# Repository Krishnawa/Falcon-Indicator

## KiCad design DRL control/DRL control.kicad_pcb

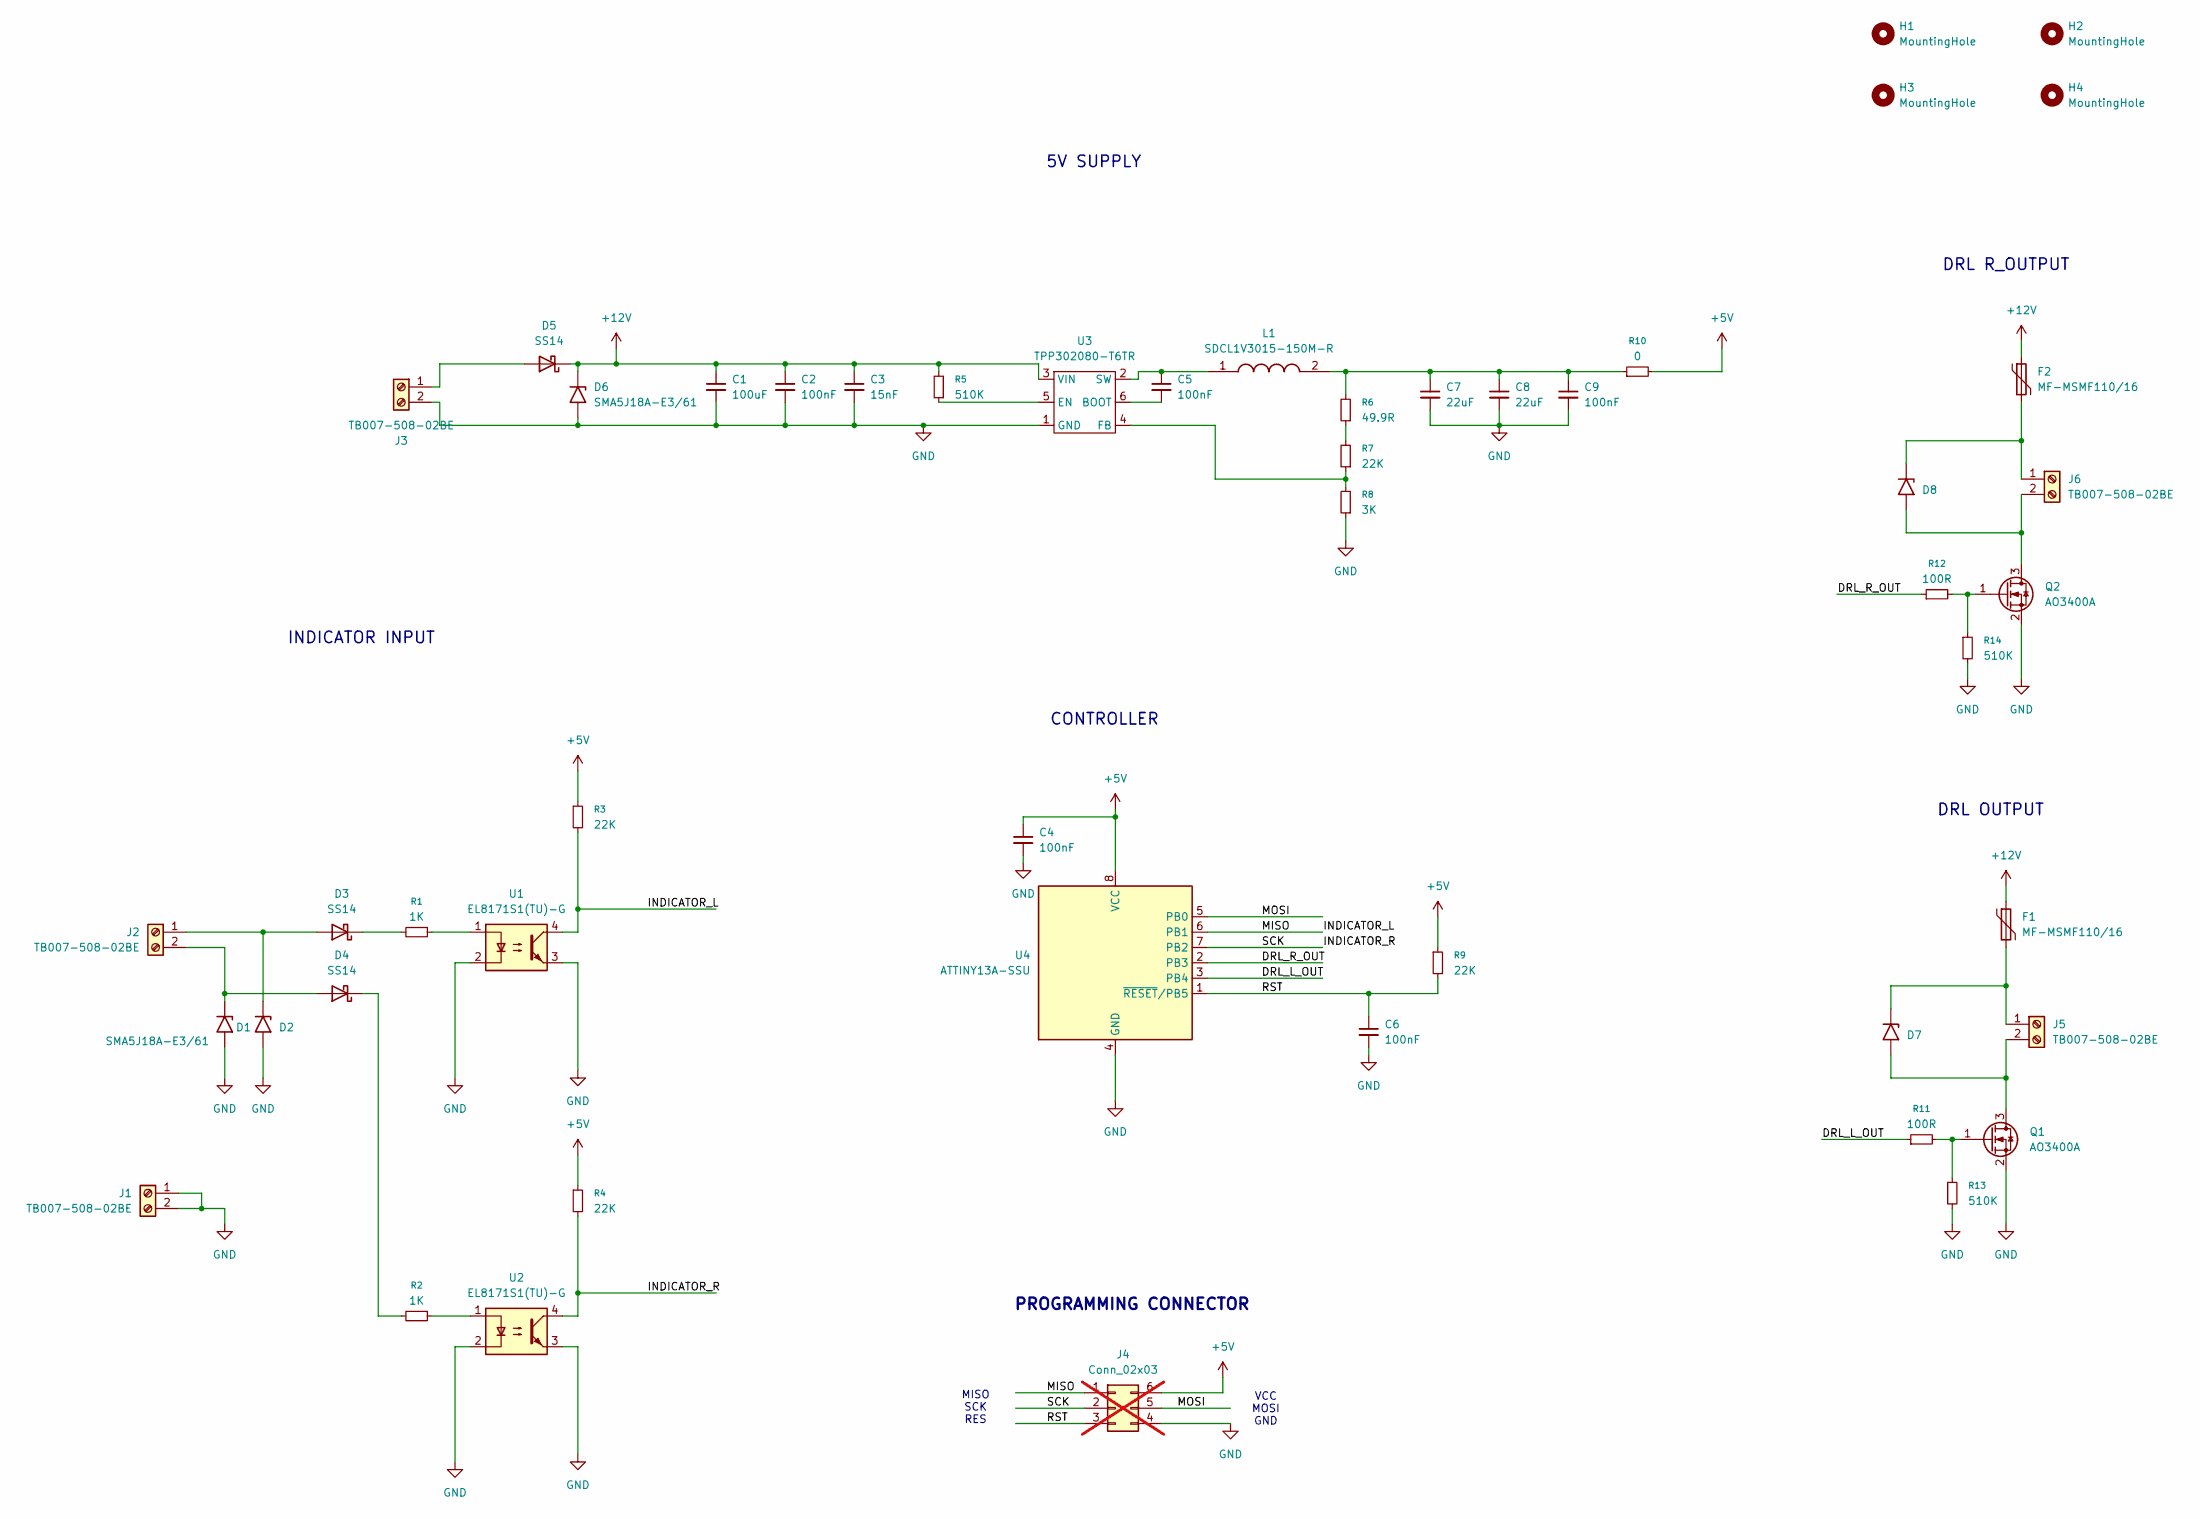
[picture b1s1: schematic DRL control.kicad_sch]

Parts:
C1: 100uF; CP_Elec_6.3x7.7; Mouser Part Number UWT1V101MCL1GS
C2, C4, C5, C6, C9: 100nF; C_0603_1608Metric_Pad1.08x0.95mm_HandSolder; Mouser Part Number CML0603X7R104KT50V
C3: 15nF; C_0603_1608Metric_Pad1.08x0.95mm_HandSolder; Mouser Part Number CGA3E2X7R1H153M080AA
C7, C8: 22uF; CP_Elec_5x3; Mouser Part Number EDH226M016S9DAA
D1, D2, D6, D7, D8: SMA5J18A-E3/61; D_SMA; Mouser Part Number SMA5J18A-E3/61
D3, D4, D5: SS14; D_SMA; Mouser Part Number SS14
F1, F2: MF-MSMF110/16; Fuse_1812_4532Metric_Pad1.30x3.40mm_HandSolder; Mouser Part Number MF-MSMF110/16
H1, H2, H3, H4: MountingHole; MountingHole_2mm
J1, J2, J3, J5, J6: TB007-508-02BE; TerminalBlock_CUI_TB007-508-02_1x02_P5.08mm_Horizontal; Mouser Part Number TB007-508-02BE
J4: Conn_02x03; IDC-Header_2x03_P2.54mm_Vertical; Mouser Part Number 826632-3; not fitted
L1: SDCL1V3015-150M-R; SDCL1V3015150MR; Mouser Part Number SDCL1V3015-150M-R
Q1, Q2: AO3400A; SOT-23; Mouser Part Number AO3400A
R1, R2: 1K; R_0805_2012Metric_Pad1.20x1.40mm_HandSolder; Mouser Part Number RK73H2ATTDD1001F
R3, R4, R7, R9: 22K; R_0603_1608Metric_Pad0.98x0.95mm_HandSolder; Mouser Part Number CR0603-FX-2202ELF
R5, R13, R14: 510K; R_0603_1608Metric_Pad0.98x0.95mm_HandSolder; Mouser Part Number RC0603FR-07510KL
R6: 49.9R; R_0603_1608Metric_Pad0.98x0.95mm_HandSolder; Mouser Part Number MCT06030C4999FP500
R8: 3K; R_0603_1608Metric_Pad0.98x0.95mm_HandSolder; Mouser Part Number ERJ-3EKF3001V
R10: 0; R_0805_2012Metric_Pad1.20x1.40mm_HandSolder; Mouser Part Number RCS08050000Z0EA
R11, R12: 100R; R_0603_1608Metric_Pad0.98x0.95mm_HandSolder; Mouser Part Number CRT0603-DY-1000ELF
U1, U2: EL8171S1(TU)-G; DIP-4_W8.89mm_SMDSocket_LongPads; Mouser Part Number EL8171S1(TU)-G
U3: TPP302080-T6TR; SOT-23-6_Handsoldering; Mouser Part Number TPP302080-T6TR
U4: ATTINY13A-SSU; SOIC-8_3.9x4.9mm_P1.27mm; Mouser Part Number ATTINY13A-SSU

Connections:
+5V: C4.1, J4.6, R3.1, R4.1, R9.1, R10.2, U4.8 (VCC)
+12V: C1.1, C2.1, C3.1, D5.1 (K), D6.1 (A1), F1.1, F2.1, R5.2, U3.3 (VIN)
/DRL_L_OUT: R11.1, U4.3 (PB4)
/DRL_R_OUT: R12.1, U4.2 (PB3)
/INDICATOR_L: J4.1, R3.2, U1.4, U4.6 (PB1)
/INDICATOR_R: J4.2, R4.2, U2.4, U4.7 (PB2)
/MOSI: J4.5, U4.5 (PB0)
/RST: C6.1, J4.3, R9.2, U4.1 (~RESET/PB5)
GND: C1.2, C2.2, C3.2, C4.2, C6.2, C7.2, C8.2, C9.2, D1.2 (A2), D2.2 (A2), D6.2 (A2), J1.1, J1.2, J3.2, J4.4, Q1.2 (S), Q2.2 (S), R8.1, R13.2, R14.2, U1.2, U1.3, U2.2, U2.3, U3.1 (GND), U4.4 (GND)
unnamed: C7.1, C8.1, C9.1, L1.2, R6.2, R10.1
unnamed: D1.1 (A1), D4.2 (A), J2.2
unnamed: D2.1 (A1), D3.2 (A), J2.1
unnamed: D3.1 (K), R1.2
unnamed: D4.1 (K), R2.2
unnamed: D5.2 (A), J3.1
unnamed: D7.1 (A1), F1.2, J5.1
unnamed: D7.2 (A2), J5.2, Q1.3 (D)
unnamed: D8.1 (A1), F2.2, J6.1
unnamed: D8.2 (A2), J6.2, Q2.3 (D)
unnamed: Q1.1 (G), R11.2, R13.1
unnamed: Q2.1 (G), R12.2, R14.1
unnamed: R1.1, U1.1
unnamed: R2.1, U2.1
unnamed: R6.1, R7.2
unnamed: C5.2, U3.6 (BOOT)
unnamed: R5.1, U3.5 (EN)
unnamed: R7.1, R8.2, U3.4 (FB)
unnamed: C5.1, L1.1, U3.2 (SW)

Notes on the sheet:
5V SUPPLY
DRL R_OUTPUT
PROGRAMMING CONNECTOR
DRL OUTPUT
VCC MOSI GND
INDICATOR INPUT
MISO SCK RES
CONTROLLER

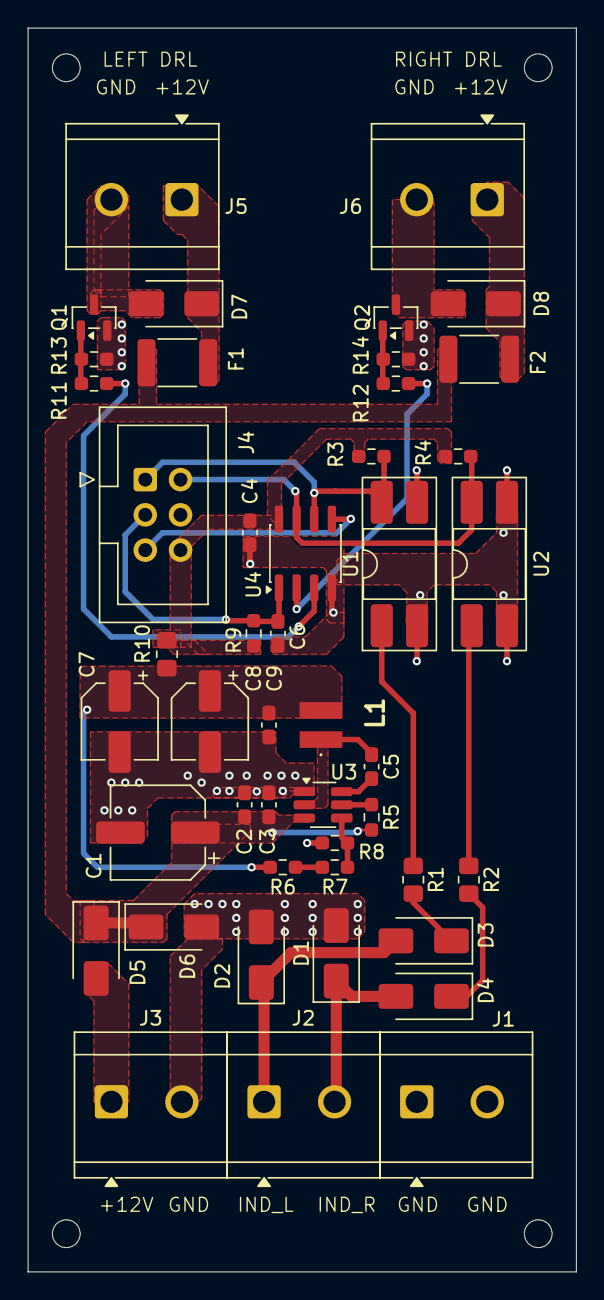
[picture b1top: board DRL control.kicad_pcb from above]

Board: 2 copper layers, 39.5 x 89.6 mm, 50 parts (0 on the bottom side), 28 nets.

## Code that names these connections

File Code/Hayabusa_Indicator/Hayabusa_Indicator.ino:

/*
 * ATTINY13A DRL Controller
 *
 * INPUTS (Active LOW)
 * PB0 - Left Indicator
 * PB1 - Right Indicator
 *
 * OUTPUTS
 * PB4 - Left DRL
 * PB3 - Right DRL
 */

#include <Arduino.h>
#include <avr/io.h>

#define LEFT_IND      PB1
#define RIGHT_IND     PB2

#define DRL_RIGHT     PB3
#define DRL_LEFT      PB4

const uint16_t OFF_TIMEOUT = 1500;   // ms

uint32_t leftLastPulse = 0;
uint32_t rightLastPulse = 0;

void setup()
{
    // Inputs
    DDRB &= ~((1 << LEFT_IND) | (1 << RIGHT_IND));

    // Enable internal pullups if needed
    // PORTB |= (1 << LEFT_IND) | (1 << RIGHT_IND);

    // Outputs
    DDRB |= (1 << DRL_LEFT) | (1 << DRL_RIGHT);

    // DRLs ON at startup
    PORTB |= (1 << DRL_LEFT) | (1 << DRL_RIGHT);

    leftLastPulse = millis();
    rightLastPulse = millis();
}

void loop()
{
    uint32_t now = millis();
    uint8_t pins = PINB;

    bool leftIndicatorOn  = !(pins & (1 << LEFT_IND));   // Active LOW
    bool rightIndicatorOn = !(pins & (1 << RIGHT_IND));  // Active LOW

    // LEFT SIDE
    if (leftIndicatorOn)
    {
        leftLastPulse = now;

        // DRL OFF
        PORTB &= ~(1 << DRL_LEFT);
    }
    else
    {
        if ((now - leftLastPulse) >= OFF_TIMEOUT)
        {
            // DRL ON
            PORTB |= (1 << DRL_LEFT);
        }
    }

    // RIGHT SIDE
    if (rightIndicatorOn)
    {
        rightLastPulse = now;

        // DRL OFF
        PORTB &= ~(1 << DRL_RIGHT);
    }
    else
    {
        if ((now - rightLastPulse) >= OFF_TIMEOUT)
        {
            // DRL ON
            PORTB |= (1 << DRL_RIGHT);
        }
    }
}
